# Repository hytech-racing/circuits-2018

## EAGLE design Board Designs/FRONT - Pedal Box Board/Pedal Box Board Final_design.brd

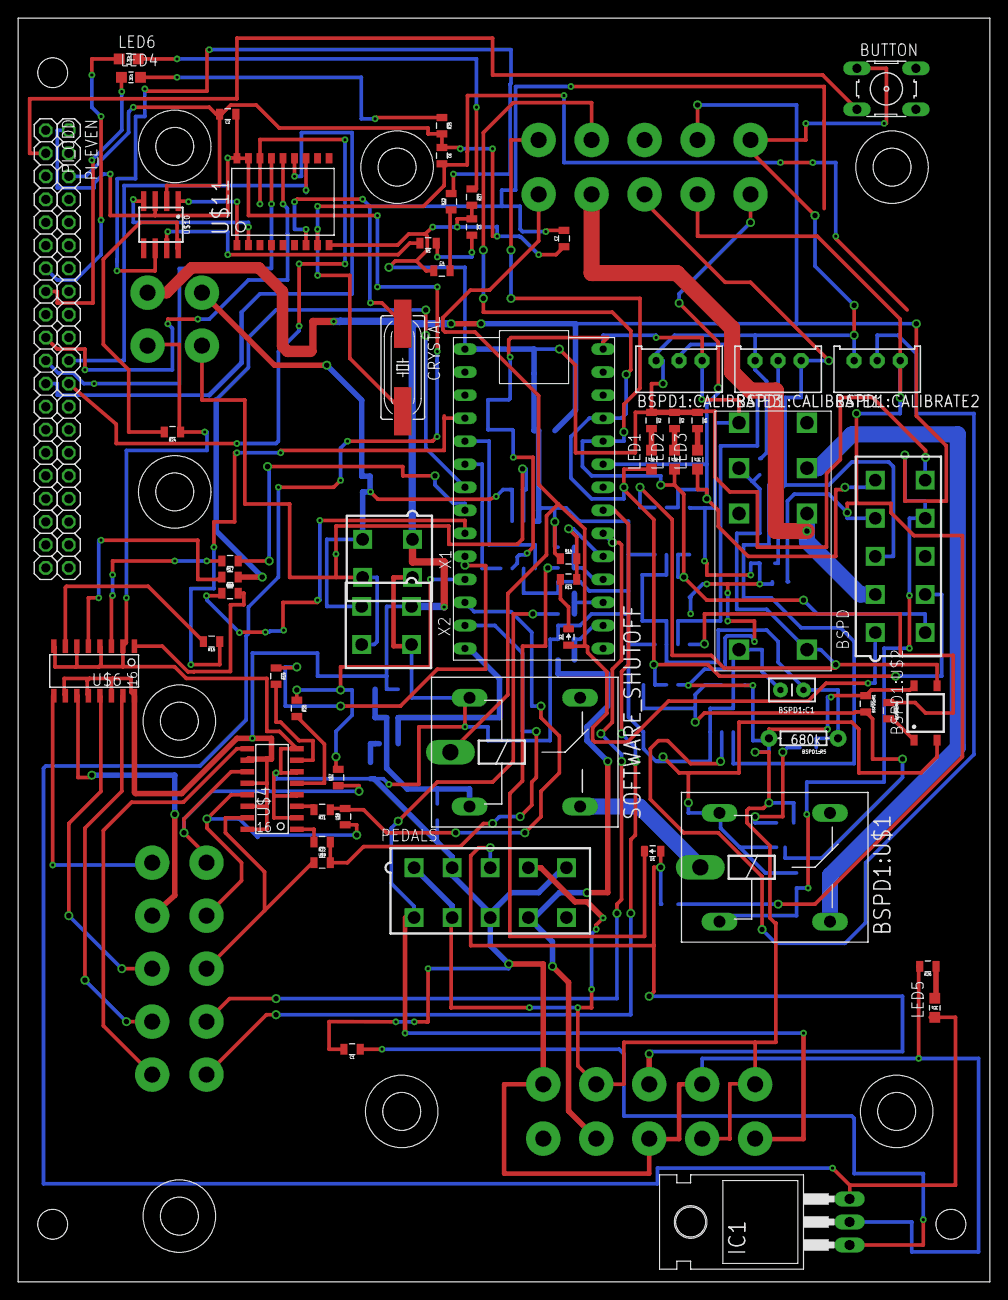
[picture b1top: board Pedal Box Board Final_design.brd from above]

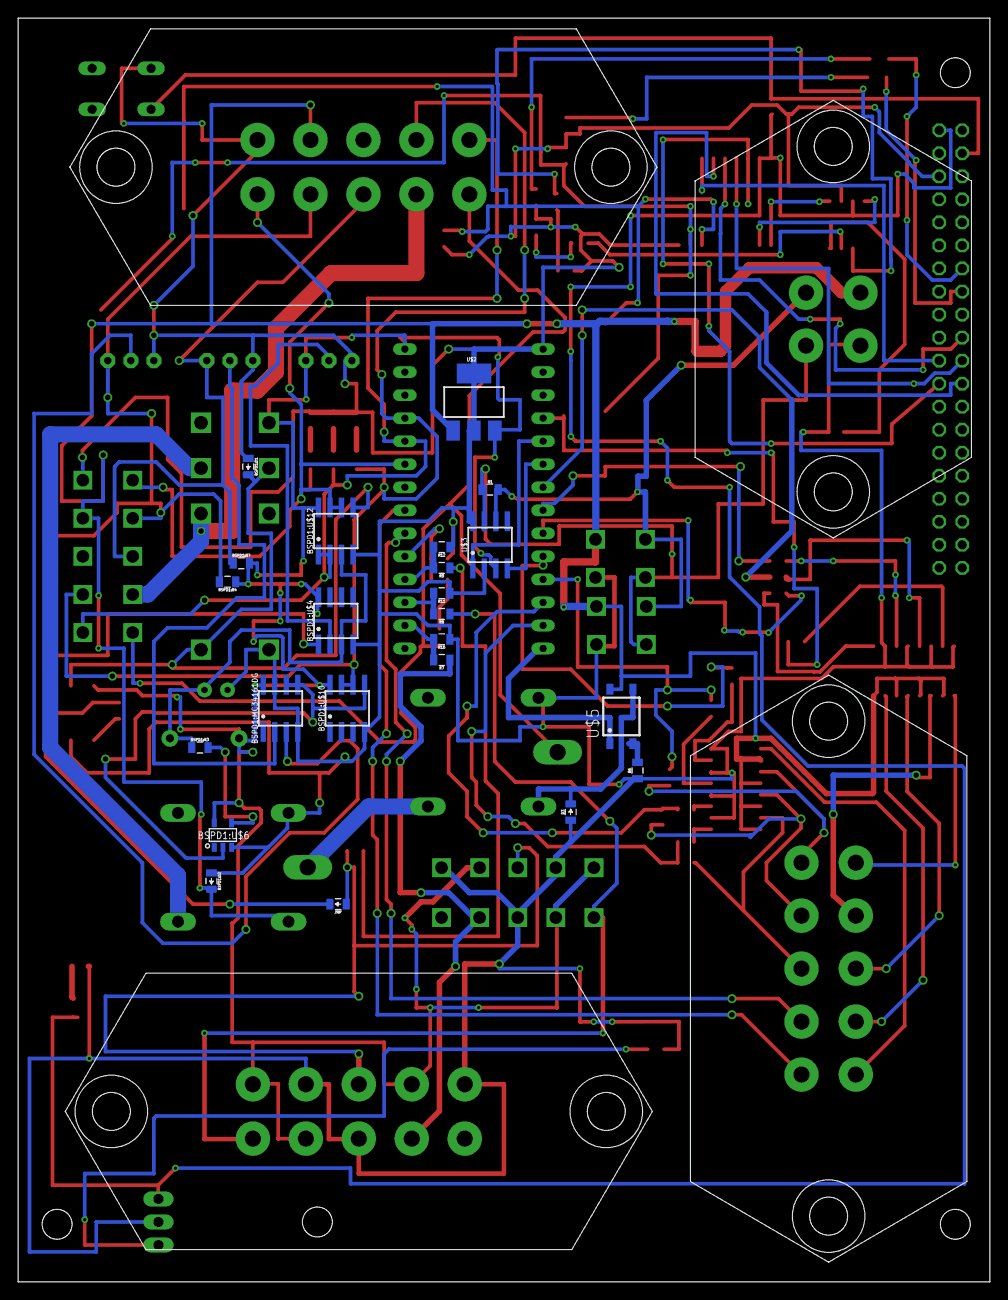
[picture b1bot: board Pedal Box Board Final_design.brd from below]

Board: 2 copper layers, 107.2 x 139.4 mm, 88 parts (27 on the bottom side), 88 nets.

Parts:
BSPD: MINIFIT_5566-10
BSPD1:C1: .47u; CAP-PTH-SMALLEZ
BSPD1:CALIBRATE1, BSPD1:CALIBRATE2, BSPD1:CALIBRATE3: TRIMPOT_3296
BSPD1:D1, BSPD1:D2: DIODE0805; 0805_D
BSPD1:MC34161DG: SOIC-08
BSPD1:R1, BSPD1:R4, BSPD1:R7: 10k; 0805
BSPD1:R3: 330; 0805
BSPD1:R5: 680k; AXIAL-0.3EZ
BSPD1:R6: 680; 0805
BSPD1:U$1: G5LE; ZF112
BSPD1:U$2: CPC1002N; SOP04
BSPD1:U$3: JW2SN-DC5V; JW2SN
BSPD1:U$4, BSPD1:U$10, BSPD1:U$12: MCP6002SOIC; SOIC-08
BSPD1:U$6: SN74LVC1G07; SOT-23-5
BUTTON: B3F-10XX
C1: .33uF; 0805
C2: .1uF; 0805
C3, C4: 560pF; 0805
C6, C7: 22pF; 0805
CRYSTAL: 16MHz; HC49UP
D1, D2, D3: DIODE0805; 0805_D
IC1: TO-220-H
JMP: DIODE0805; 0805_D
LED1, LED2, LED3, LED4, LED5, LED6: LED-805
PEDALS: MINIFIT_5566-10
PI_EVEN: 1X20
PI_ODD: 1X20
R1: 120; 0805
R2, R3, R4, R25, R26, R27: 150; 0805
R5, R6, R23: 100; 0805
R7, R8, R9: 10k; 0805
R10, R11, R12: 15k; 0805
R13: 43k; 0805
R14: 12k; 0805
R15, R16, R17, R18, R19, R20, R21, R22: 270; 0805
R24: 4.7k; 0805
SOFTWARE_SHUTOFF: G5LE; ZF112
U$1: TEENSY_3.2_SIMPLE
U$2: SOT223
U$3, U$10: MCP2551; SOIC-08
U$4, U$6: TLP291-4; SOIC-16
U$5: CPC1002N; SOP04
U$7, U$8, U$9: JUMPER; 0805
U$11: MCP2515SMD; SOIC-18W
X1, X2: MINIFIT_5566-4
X3: CONNECTOR-4MX150L_VERTICAL-4; MX150L_VERTICAL-4
X4, X5, X6: CONNECTOR-10MX150L_VERTICAL-10; MX150L_VERTICAL-10

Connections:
+5V: BSPD1:CALIBRATE3.1, BSPD1:MC34161DG.8, BSPD1:R1.1, BSPD1:R4.1, BSPD1:R5.P$2, BSPD1:R7.2, BSPD1:U$2.4, BSPD1:U$3.4, BSPD1:U$4.8, BSPD1:U$6.5, BSPD1:U$10.8, BSPD1:U$12.8, PEDALS.1, PEDALS.4, PEDALS.7, U$1.VIN, U$2.3, U$3.3, X4.1, X4.4, X4.7
+5V/1: C2.1, IC1.3, LED5.A, PI_EVEN.1, U$10.3, U$11.17, U$11.18
+12V: BSPD.9, BSPD1:D2.C, BSPD1:U$1.2, U$2.1, U$4.10, U$4.12, U$4.14, U$4.16, U$5.4, U$6.10, U$6.12, U$6.14, U$6.16, X1.1, X2.1, X3.1, X5.9
BSPD1:N$1: BSPD1:D1.C, BSPD1:U$2.3, BSPD1:U$3.3, BSPD1:U$3.COIL-, BSPD1:U$12.5
BSPD1:N$2: BSPD1:R3.2, BSPD1:U$6.4
BSPD1:N$3: BSPD1:R6.2, BSPD1:U$2.1
BSPD1:N$5: BSPD1:CALIBRATE2.2, BSPD1:MC34161DG.3
BSPD1:N$6: BSPD1:CALIBRATE1.2, BSPD1:MC34161DG.2
BSPD1:N$7: BSPD1:CALIBRATE3.2, BSPD1:U$4.2
BSPD1:N$9: BSPD1:R6.1, BSPD1:U$4.1
BSPD1:N$10: BSPD1:MC34161DG.5, BSPD1:MC34161DG.6, BSPD1:R1.2, BSPD1:U$6.2, BSPD1:U$10.5
BSPD1:N$13: BSPD1:C1.1, BSPD1:R3.1, BSPD1:R5.P$1, BSPD1:U$4.3, BSPD1:U$12.3
BSPD1:SHUTDOWN_C: BSPD1:U$1.S, BSPD1:U$3.6
BUT: BUTTON.3, PI_ODD.2
CAN-H: R5.2, U$10.7
CAN-L: R23.2, U$10.6
CS: PI_EVEN.12, U$11.16
GND: BSPD.10, BSPD1:C1.2, BSPD1:CALIBRATE1.3, BSPD1:CALIBRATE2.3, BSPD1:CALIBRATE3.3, BSPD1:D1.A, BSPD1:D2.A, BSPD1:MC34161DG.4, BSPD1:MC34161DG.7, BSPD1:U$1.1, BSPD1:U$2.2, BSPD1:U$3.COIL+, BSPD1:U$4.4, BSPD1:U$6.3, BSPD1:U$10.4, BSPD1:U$12.4, BUTTON.1, C1.2, C2.2, C3.1, C4.1, C6.1, C7.1, D3.A, IC1.2, PEDALS.2, PEDALS.5, PEDALS.8, PI_EVEN.3, R2.1, R3.1, R4.1, R6.1, R10.1, R11.1, R12.1, R14.1, R24.1, R25.2, R26.2, R27.2, SOFTWARE_SHUTOFF.1, U$1.GND, U$2.2, U$2.4, U$3.2, U$3.8, U$4.2, U$4.4, U$4.6, U$4.8, U$6.2, U$6.4, U$6.6, U$6.8, U$10.2, U$11.9, X1.2, X2.2, X3.2, X4.2, X4.5, X4.8, X5.10
INT: PI_EVEN.11, U$11.12
LED1: LED4.A, PI_ODD.8
LED2: LED6.A, PI_ODD.7
MISO: PI_ODD.11, U$11.15
MOSI: PI_ODD.10, U$11.14
unnamed: PEDALS.9, R7.1, X4.9
unnamed: U$1.D4(CANRX), U$3.4
unnamed: R1.2, U$3.6, X1.3, X2.3, X3.3
unnamed: R1.1, U$3.7, X1.4, X2.4, X3.4
unnamed: U$1.D3(CANTX), U$3.1
unnamed: R8.2, R11.2, U$1.A1
unnamed: D1.C, R9.1
unnamed: PEDALS.6, R8.1, X4.6
unnamed: R7.2, R10.2, U$1.A0
unnamed: R9.2, R12.2, U$1.A2
unnamed: D1.A, JMP.A, PEDALS.3, X4.3
unnamed: D3.C, SOFTWARE_SHUTOFF.2, U$5.3
unnamed: D2.C, R13.2
unnamed: LED1.C, R2.2
unnamed: LED2.C, R3.2
unnamed: LED3.C, R4.2
unnamed: R21.1, U$1.D10(TX2), U$8.2
unnamed: R17.1, U$1.D6
unnamed: R15.2, U$6.7
unnamed: R15.1, U$1.D2
unnamed: R16.1, U$1.D5
unnamed: R6.2, U$5.2
unnamed: R18.1, U$1.D7(RX3)
unnamed: R16.2, U$6.5
unnamed: R20.1, U$1.D9(RX2), U$7.2
unnamed: R22.1, U$1.D11, U$9.2
unnamed: R21.2, U$4.3
unnamed: R17.2, U$6.3
unnamed: R18.2, U$6.1
unnamed: R19.1, U$1.D8(TX3)
unnamed: R19.2, U$4.7
unnamed: R20.2, U$4.5
unnamed: U$1.A5, X6.10
unnamed: U$1.A4, X6.9
unnamed: R22.2, U$4.1
unnamed: U$4.13, U$8.1, X6.7
unnamed: U$10.1, U$11.1
unnamed: U$4.15, U$9.1, X6.8
unnamed: U$10.4, U$11.2
unnamed: C6.2, CRYSTAL.2, U$11.8
unnamed: R24.2, U$10.8
unnamed: C7.2, CRYSTAL.1, U$11.7
unnamed: C3.2, R5.1
unnamed: U$6.9, X6.1
unnamed: U$6.11, X6.2
unnamed: U$6.13, X6.3
unnamed: U$6.15, X6.4
unnamed: U$4.9, X6.5
unnamed: U$4.11, U$7.1, X6.6
unnamed: C4.2, R23.1
unnamed: C1.1, IC1.1
unnamed: LED4.C, R25.1
unnamed: LED5.C, R26.1
unnamed: LED6.C, R27.1
READ_CHARGE: BSPD.6, BSPD1:U$12.1, BSPD1:U$12.2, LED2.A, U$1.A8, X5.6
READ_FAULT: BSPD.5, BSPD1:U$12.6, BSPD1:U$12.7, LED3.A, U$1.A7, X5.5
READ_SWITCH: BSPD.7, BSPD1:U$10.6, BSPD1:U$10.7, LED1.A, U$1.A9, X5.7
READ_UPSTREAM_SHUTDOWN: R13.1, R14.2, U$1.A3
SCK: PI_ODD.12, U$11.13
SHUTDOWN_A: BSPD.1, D2.A, SOFTWARE_SHUTOFF.P, X5.1
SHUTDOWN_B: BSPD1:U$1.P, SOFTWARE_SHUTOFF.S
SHUTDOWN_D: BSPD.2, BSPD1:U$3.7, X5.2
SHUTDOWN_RELAY_CTRL: U$1.D12, U$5.1
SIGNAL_BRAKE: BSPD.4, BSPD1:CALIBRATE2.1, BSPD1:R4.2, JMP.C, X5.4
SIGNAL_CURRENT: BSPD.3, BSPD1:CALIBRATE1.1, BSPD1:R7.1, X5.3

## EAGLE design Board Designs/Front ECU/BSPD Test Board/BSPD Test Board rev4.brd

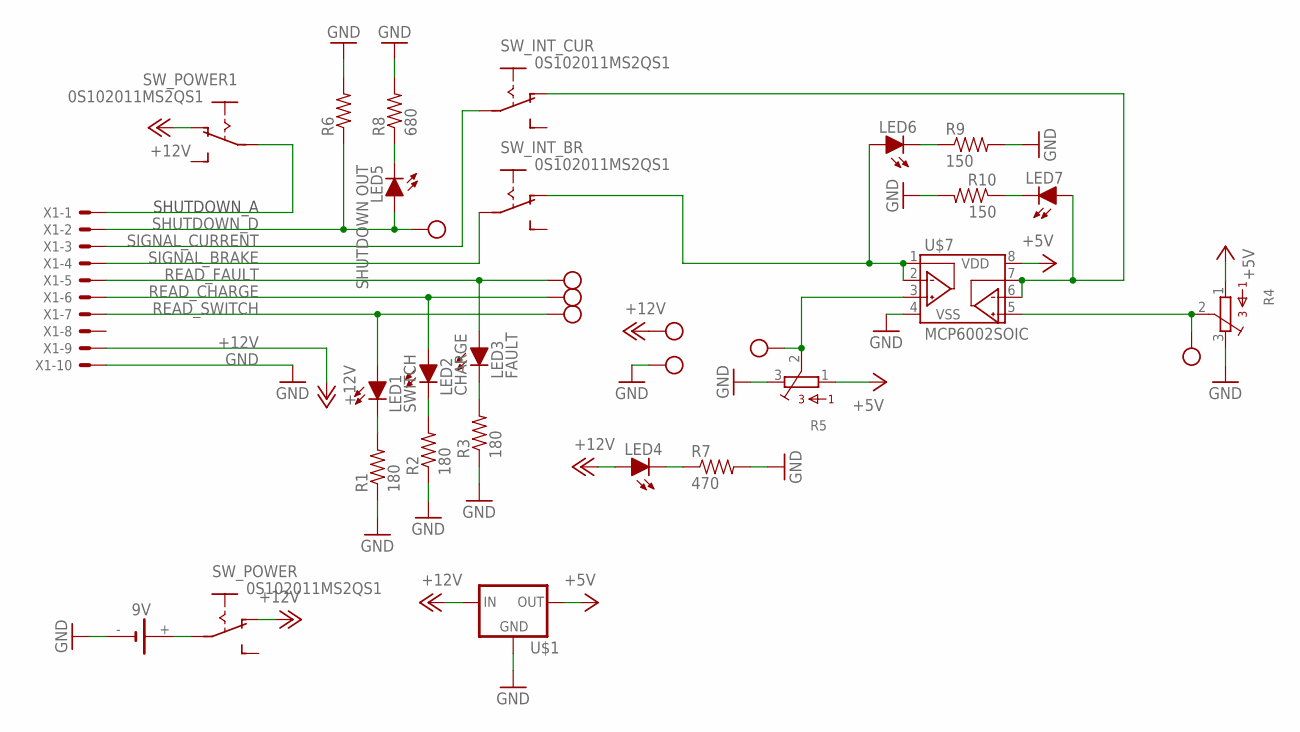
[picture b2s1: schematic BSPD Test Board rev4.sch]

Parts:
9V: 1291-79
LED1: SWITCH; LED-5MM
LED2: CHARGE; LED-5MM
LED3: FAULT; LED-5MM
LED4, LED6, LED7: LED-0805; LED-805
LED5: SHUTDOWN OUT; LED-5MM
R1, R2, R3: 180; 0805
R4, R5: TRIMPOT_3296C; TRIMPOT_3296
R6: RESISTORPTH-1/2W; AXIAL-0.5
R7: 470; 0805
R8: 680; 0805
R9, R10: 150; 0805
SW_INT_BR: 0S102011MS2QS1
SW_INT_CUR: 0S102011MS2QS1
SW_POWER, SW_POWER1: 0S102011MS2QS1
U$1: 5VREG_LM340-NLM340MPX-5.0/NOPB; SOT223
U$2, U$3, U$4, U$5, U$6, U$8, U$9, U$10: TEST_POINT
U$7: MCP6002SOIC; SOIC-08
X1: CONNECTOR-10; MINIFIT_5566-10

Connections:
+5V: R4.1, R5.1, U$1.3 (OUT), U$7.8 (VDD)
+12V: LED4.A, SW_POWER.P$1 (O), SW_POWER1.P$1 (O), U$1.1 (IN), U$5.P$1, X1.9
GND: 9V.-, R1.1, R2.1, R3.1, R4.3, R5.3, R6.P$2 (2), R7.2, R8.2, R9.2, R10.2, U$1.2 (GND), U$1.4 (GND), U$6.P$1, U$7.4 (VSS), X1.10
unnamed: LED1.K (C), R1.2
unnamed: LED2.K (C), R2.2
unnamed: LED3.K (C), R3.2
unnamed: R4.2, U$2.P$1, U$7.5 (VINB+)
unnamed: R5.2, U$3.P$1, U$7.3 (VINA+)
unnamed: 9V.+, SW_POWER.P$2
unnamed: LED4.C, R7.1
unnamed: LED6.A, SW_INT_BR.P$1 (O), U$7.1 (VOUTA), U$7.2 (VINA-)
unnamed: LED7.A, SW_INT_CUR.P$1 (O), U$7.6 (VINB-), U$7.7 (VOUTB)
unnamed: LED6.C, R9.1
unnamed: LED5.K (C), R8.1
unnamed: LED7.C, R10.1
unnamed: SW_POWER1.P$2, X1.1
READ_CHARGE: LED2.A, U$9.P$1, X1.6
READ_FAULT: LED3.A, U$8.P$1, X1.5
READ_SWITCH: LED1.A, U$10.P$1, X1.7
SHUTDOWN_D: LED5.A, R6.P$1 (1), U$4.P$1, X1.2
SIGNAL_BRAKE: SW_INT_BR.P$2, X1.4
SIGNAL_CURRENT: SW_INT_CUR.P$2, X1.3

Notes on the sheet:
SHUTDOWN_A

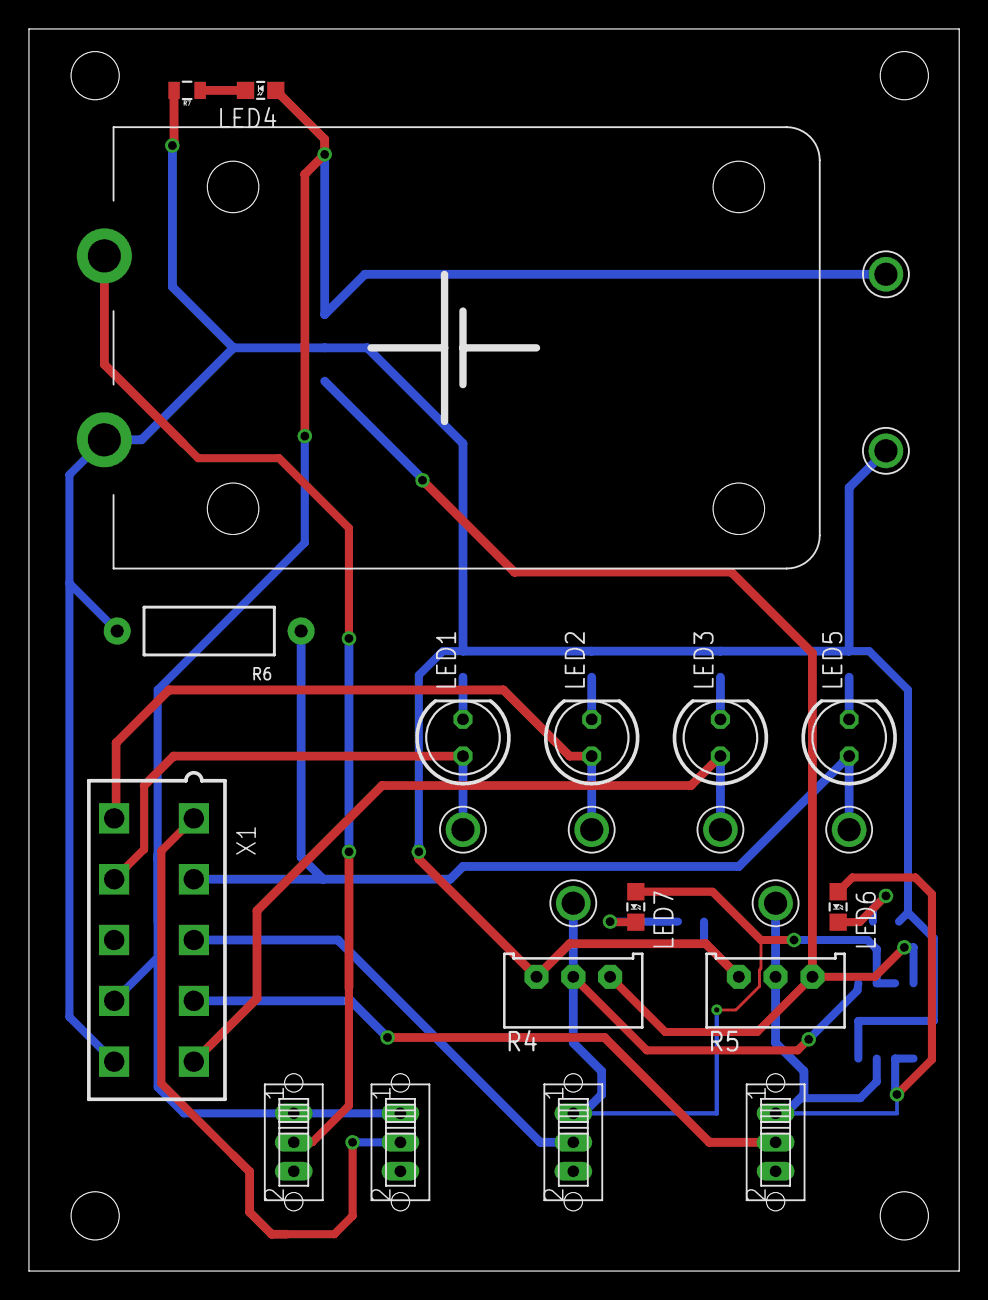
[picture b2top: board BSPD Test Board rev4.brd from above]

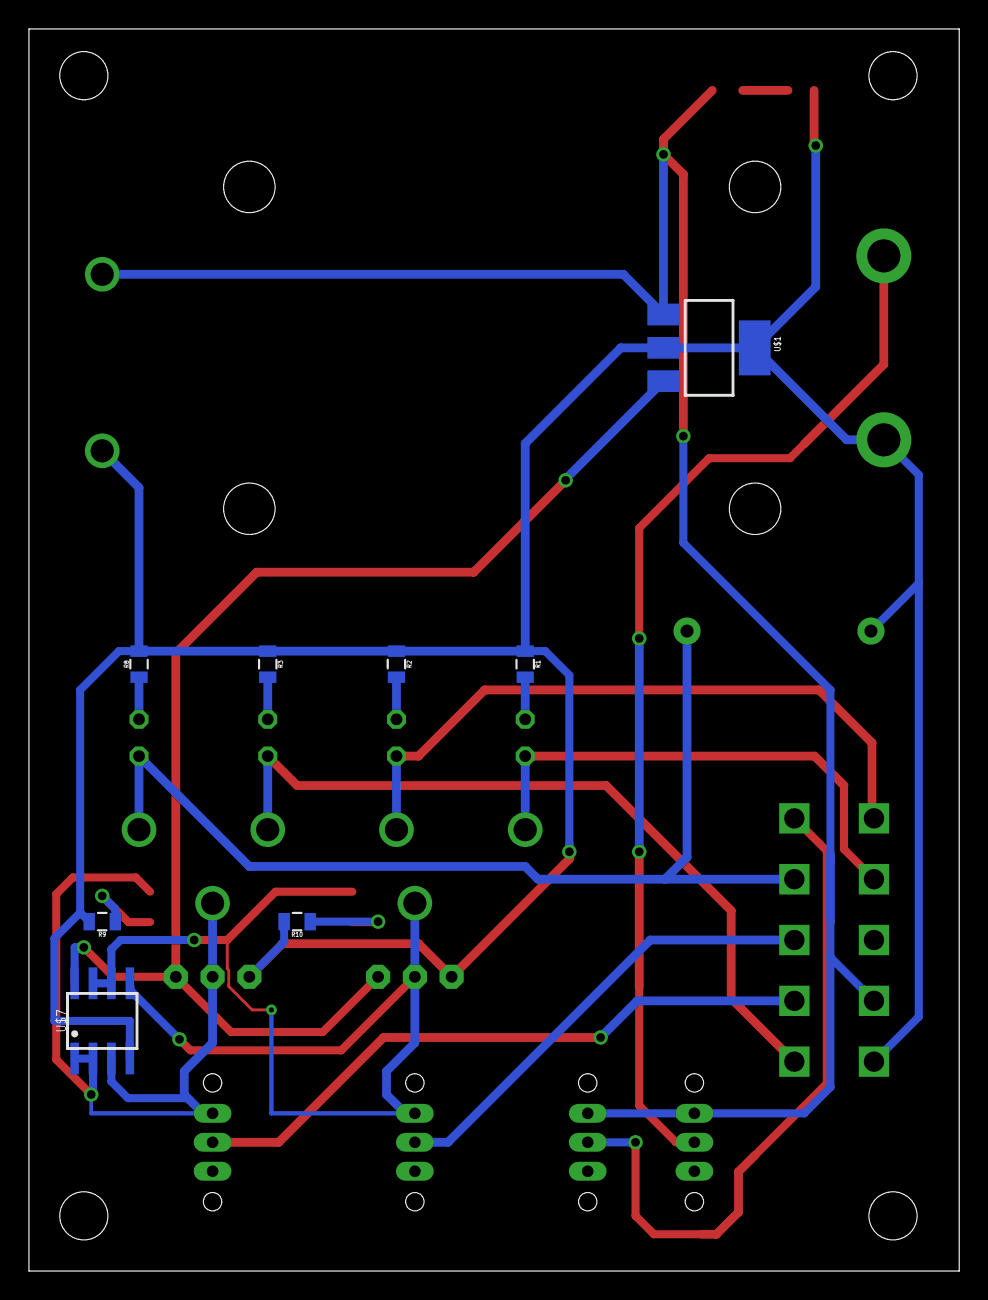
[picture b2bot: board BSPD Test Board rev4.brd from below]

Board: 2 copper layers, 64.2 x 85.8 mm, 33 parts (8 on the bottom side), 22 nets.

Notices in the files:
parts and their libraries:
SparkFun-FreqCtrl: Licensing: Creative Commons ShareAlike 4.0 International - https://creativecommons.org/licenses/by-sa/4.0
